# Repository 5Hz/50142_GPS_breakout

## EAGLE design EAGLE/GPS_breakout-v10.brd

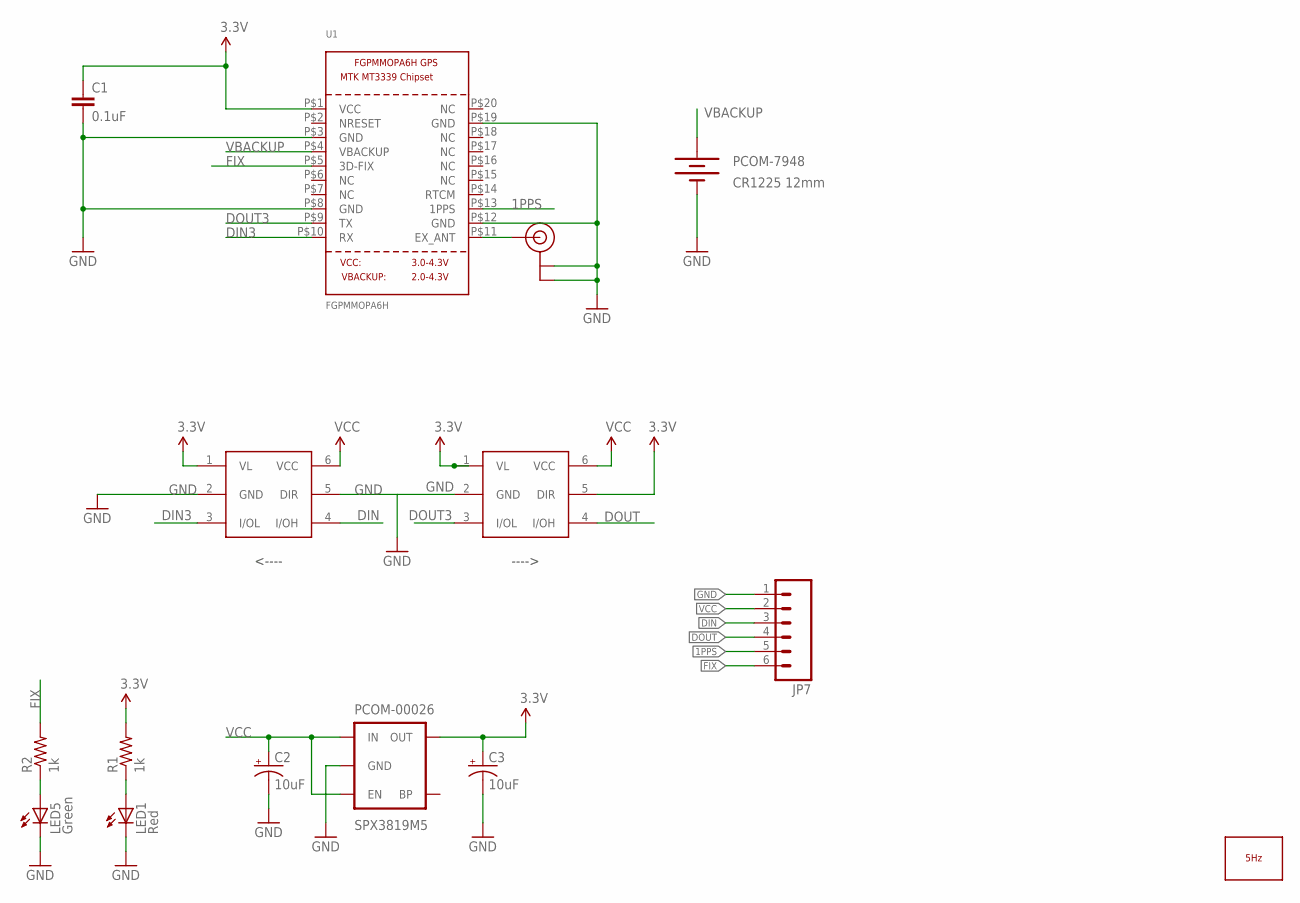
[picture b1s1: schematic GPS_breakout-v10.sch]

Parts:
C1: 0.1uF; 0603-CAP
C2, C3: 10uF; EIA3216
JP7: M06SIP; 1X06
LED1: Red; LED-0603
LED5: Green; LED-0603
LOGO1: LOGO_5HZ_MAIN_15MM; 5HZ_LOGO_MAIN_15MM
PCOM-00026: SPX3819M5; SOT23-5
PCOM-7948: CR1225 12mm; BATTCON_12MM_PTH
R1, R2: 1k; 0603-RES
U1: FGPMMOPA6H
U$7, U$8: MAX337; SOT-363
U$20: U.FL

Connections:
1PPS: JP7.5, U1.P$13 (1PPS)
3.3V: C1.1, C3.A (+), PCOM-00026.5 (OUT), R1.2, U1.P$1 (VCC), U$7.1 (VL), U$8.1 (VL), U$8.5 (DIR)
DIN: JP7.3, U$7.4 (I/OH)
DIN3: U1.P$10 (RX), U$7.3 (I/OL)
DOUT: JP7.4, U$8.4 (I/OH)
DOUT3: U1.P$9 (TX), U$8.3 (I/OL)
FIX: JP7.6, R2.2, U1.P$5 (3D-FIX)
GND: C1.2, C2.C (-), C3.C (-), JP7.1, LED1.C, LED5.C, PCOM-00026.2 (GND), PCOM-7948.GND (-), U1.P$3 (GND), U1.P$8 (GND), U1.P$12 (GND), U1.P$19 (GND), U$7.2 (GND), U$7.5 (DIR), U$8.2 (GND), U$20.P$1 (GND), U$20.P$2 (GND)
unnamed: LED1.A, R1.1
unnamed: U1.P$11 (EX_ANT), U$20.P$3 (SIGNAL)
unnamed: LED5.A, R2.1
VBACKUP: PCOM-7948.VCC@1 (+), U1.P$4 (VBACKUP)
VCC: C2.A (+), JP7.2, PCOM-00026.1 (IN), PCOM-00026.3 (EN), U$7.6 (VCC), U$8.6 (VCC)

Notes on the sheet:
<----
---->

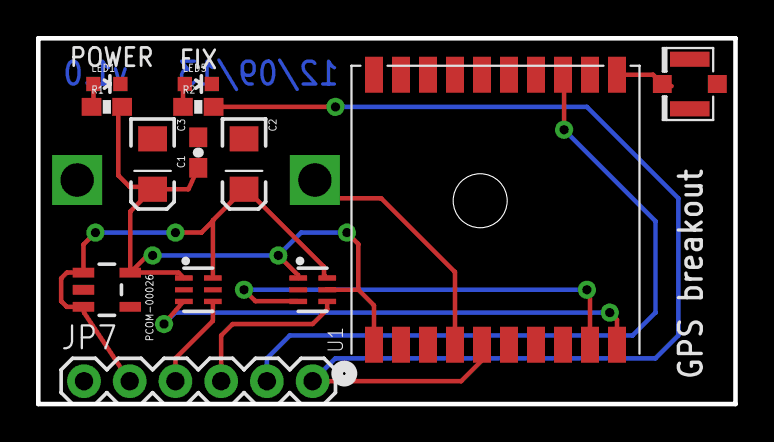
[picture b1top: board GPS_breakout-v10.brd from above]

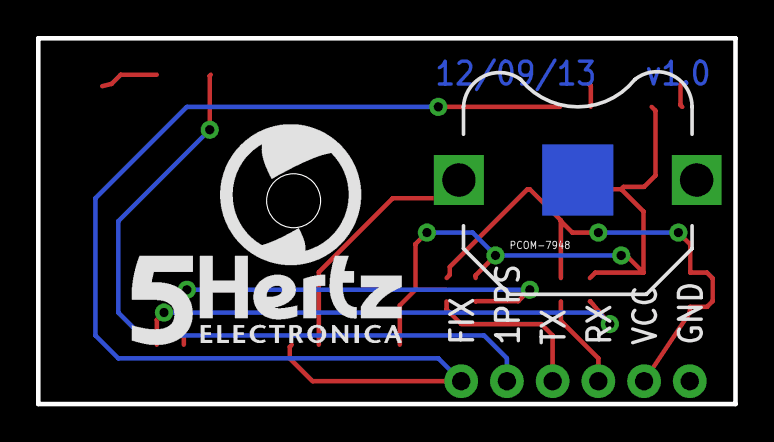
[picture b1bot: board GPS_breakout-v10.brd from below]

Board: 2 copper layers, 38.7 x 20.3 mm, 15 parts (2 on the bottom side), 13 nets.

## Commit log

2014-10-22 :lollipop: Added .gitattributes
2014-10-22 GPS_5Hz
    Agregada librería GPS_5Hz para utilizar con la tarjeta breakout
